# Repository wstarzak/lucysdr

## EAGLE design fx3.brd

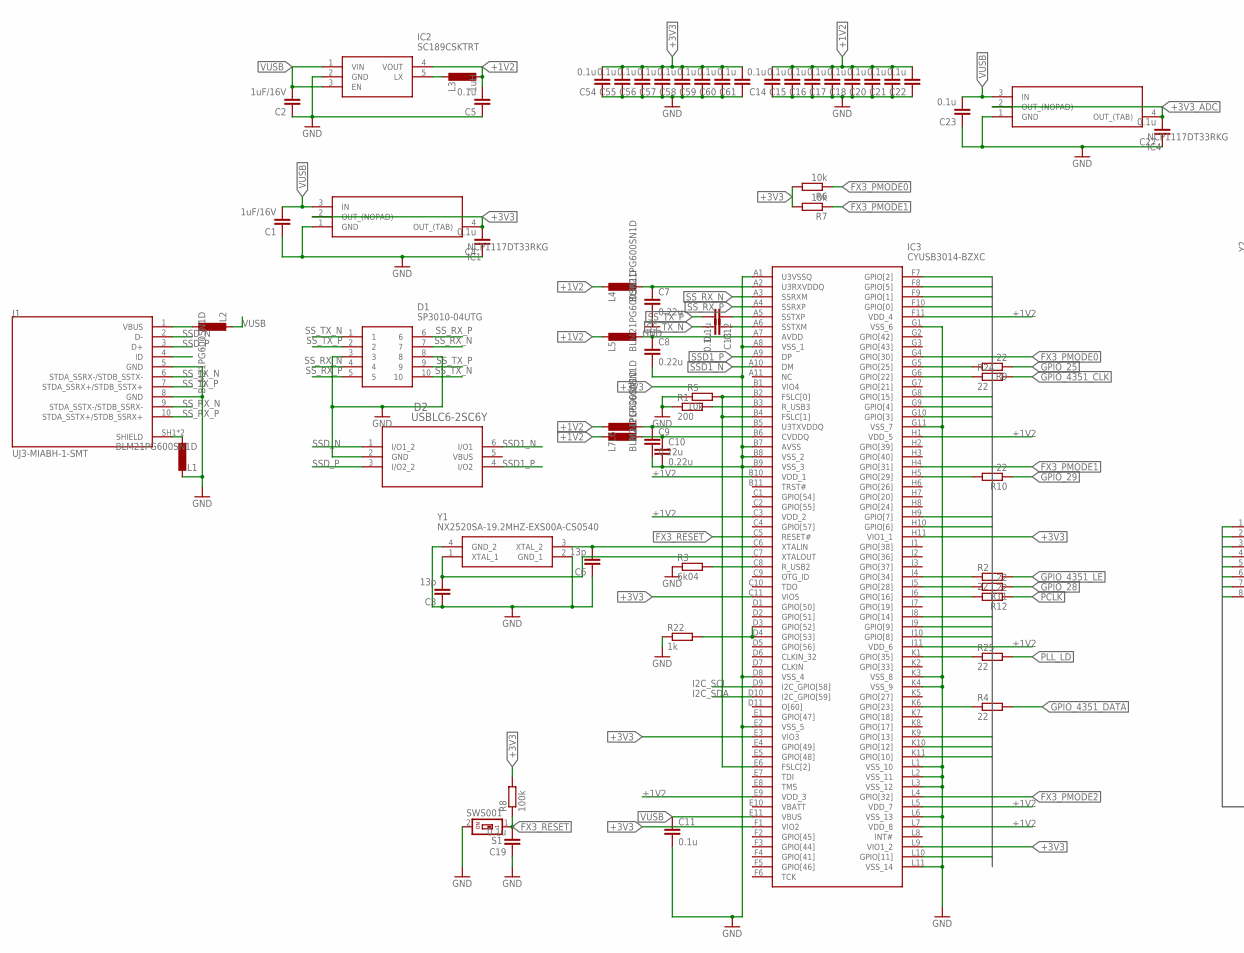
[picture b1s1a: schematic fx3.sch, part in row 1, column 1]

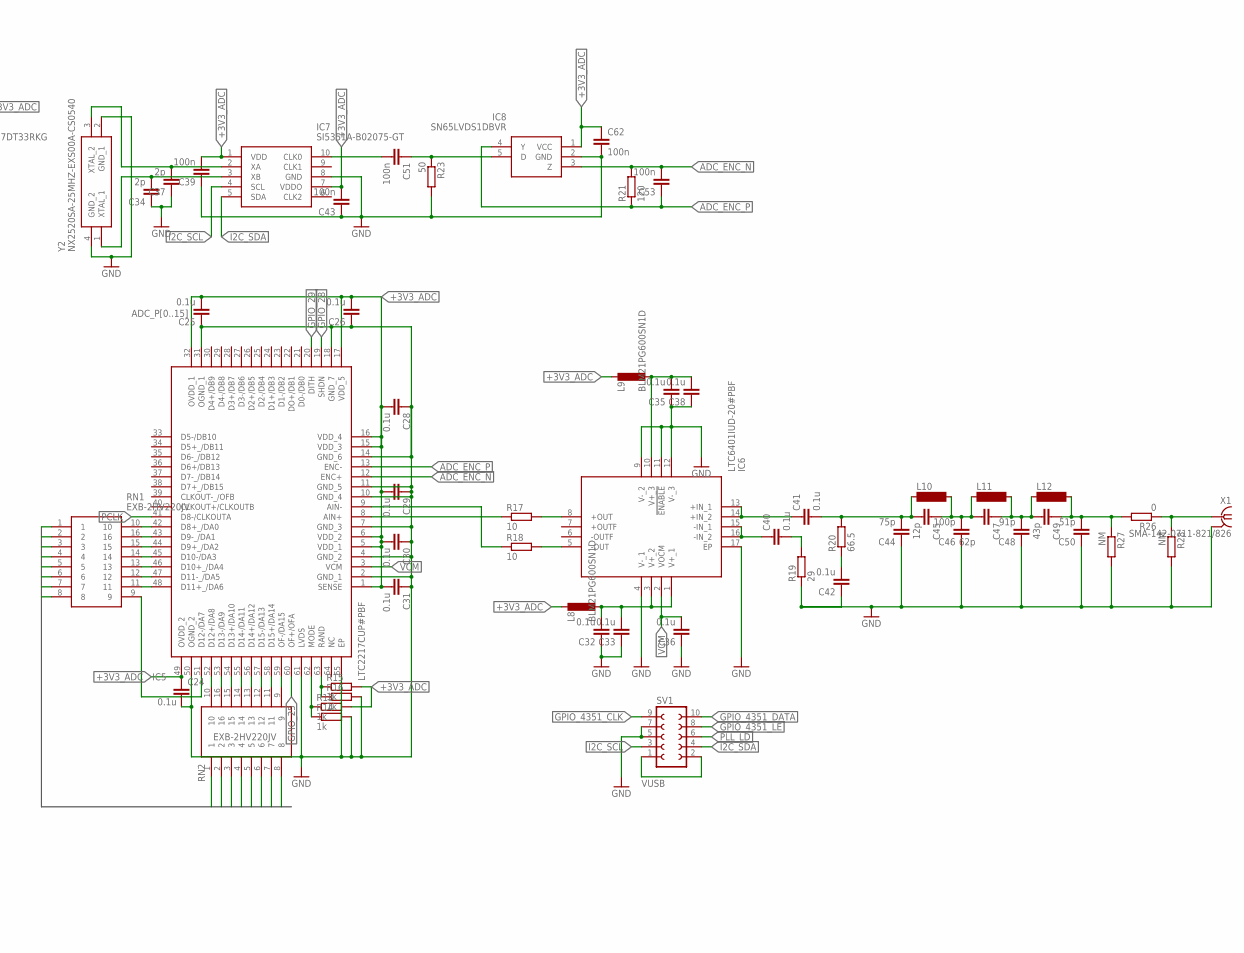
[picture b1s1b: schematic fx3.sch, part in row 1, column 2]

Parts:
C1, C2: 1uF/16V; C0603
C3, C6: 13p; C0603
C4, C5, C11, C12, C13, C14, C15, C16, C17, C18, C19, C20, C21, C22, C23, C24, C25, C26, C27, C28, C29, C30, C31, C32, C33, C35, C36, C38, C40, C41, C42, C54, C55, C56, C57, C58, C59, C60, C61: 0.1u; C0603
C7, C8, C9, C10: 0.22u; C0603
C34, C37: 2p; C0603
C39, C43, C51, C53, C62: 100n; C0603
C44: 75p; C0603
C45: 12p; C0603
C46: 100p; C0603
C47: 62p; C0603
C48: 91p; C0603
C49: 43p; C0603
C50: 51p; C0603
D1: SP3010-04UTG; UDFN-10
D2: USBLC6-2SC6Y; SOT23-6L_STM
IC1, IC4: NCP1117DT33RKG; TO229P990X238-4N
IC2: SC189CSKTRT; SOT95P280X145-5N
IC3: CYUSB3014-BZXC; BGA121C80P11X11_1000X1000X120
IC5: LTC2217CUP#PBF; QFN50P900X900X80-65N
IC6: LTC6401IUD-20#PBF; QFN50P300X300X80-17N
IC7: SI5351A-B02075-GT; SOP50P490X110-10N
IC8: SN65LVDS1DBVR; SOT95P280X145-5N
J1: UJ3-MIABH-1-SMT; CUI_UJ3-MIABH-1-SMT
L1, L2, L4, L5, L6, L7, L8, L9: BLM21PG600SN1D; BLM21AG102BH1J
L3: 1uH; BLM21AG102BH1J
L10, L11, L12: MS85
R1: 200; R0603
R2, R4, R9, R10, R11, R12, R24, R25: 22; R0603
R3: 6k04; R0603
R5, R6, R7: 10k; R0603
R8: 100k; R0603
R13, R14, R15, R16, R22: 1k; R0603
R17, R18: 10; R0603
R19: 29; R0603
R20: 66.5; R0603
R21: 120; R0603
R23: 50; R0603
R26: 0; R0603
R27, R28: NM; R0603
RN1, RN2: EXB-2HV220JV; EXB2HV220JV
S1: SWS001; SMS-001
SV1: FE05-2
X1: SMA-142-0711-821/826; J502-ND-142-0711-821/826
Y1: NX2520SA-19.2MHZ-EXS00A-CS0540; NX2520SA192MHZEXS00ACS05400
Y2: NX2520SA-25MHZ-EXS00A-CS0540; NX2520SA192MHZEXS00ACS05400

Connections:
+1V2: C5.2, C14.2, C15.2, C16.2, C17.2, C18.2, C20.2, C21.2, C22.2, IC2.4 (VOUT), IC3.B10 (VDD_1), IC3.C3 (VDD_2), IC3.E9 (VDD_3), IC3.F11 (VDD_4), IC3.H1 (VDD_5), IC3.J11 (VDD_6), IC3.L5 (VDD_7), IC3.L7 (VDD_8), L3.2, L4.1, L5.1, L6.1, L7.1
+3V3: C4.2, C54.2, C55.2, C56.2, C57.2, C58.2, C59.2, C60.2, C61.2, IC1.2 (OUT_(NOPAD)), IC1.4 (OUT_(TAB)), IC3.B1 (VIO4), IC3.C11 (VIO5), IC3.E3 (VIO3), IC3.F1 (VIO2), IC3.H11 (VIO1_1), IC3.L9 (VIO1_2), R6.2, R7.2, R8.2
+3V3_ADC: C24.1, C25.2, C26.2, C27.2, C28.2, C29.2, C30.2, C31.2, C39.2, C43.2, C62.1, IC4.2 (OUT_(NOPAD)), IC4.4 (OUT_(TAB)), IC5.1 (SENSE), IC5.5 (VDD_1), IC5.6 (VDD_2), IC5.15 (VDD_3), IC5.16 (VDD_4), IC5.17 (VDD_5), IC5.32 (OVDD_1), IC5.49 (OVDD_2), IC7.1 (VDD), IC7.7 (VDDO), IC8.1 (VCC), L8.1, L9.1, R13.2, R15.2
ADC_ENC_N: C53.2, IC5.12 (ENC+), IC8.3 (Z), R21.2
ADC_ENC_P: C53.1, IC5.13 (ENC-), IC8.4 (Y), R21.1
ADC_P0: IC3.F10 (GPIO[0]), RN1.1
ADC_P1: IC3.F9 (GPIO[1]), RN1.2
ADC_P2: IC3.F7 (GPIO[2]), RN1.3
ADC_P3: IC3.G10 (GPIO[3]), RN1.4
ADC_P4: IC3.G9 (GPIO[4]), RN1.5
ADC_P5: IC3.F8 (GPIO[5]), RN1.6
ADC_P6: IC3.H10 (GPIO[6]), RN1.7
ADC_P7: IC3.H9 (GPIO[7]), RN1.8
ADC_P8: IC3.J10 (GPIO[8]), RN2.1
ADC_P9: IC3.J9 (GPIO[9]), RN2.2
ADC_P10: IC3.K11 (GPIO[10]), RN2.3
ADC_P11: IC3.L10 (GPIO[11]), RN2.4
ADC_P12: IC3.K10 (GPIO[12]), RN2.5
ADC_P13: IC3.K9 (GPIO[13]), RN2.6
ADC_P14: IC3.J8 (GPIO[14]), RN2.7
ADC_P15: IC3.G8 (GPIO[15]), RN2.8
AVDD_A7: C8.1, IC3.A7 (AVDD), L5.2
CVDDQ_B6: C10.1, IC3.B6 (CVDDQ), L7.2
FX3_PMODE0: IC3.G4 (GPIO[30]), R6.1
FX3_PMODE1: IC3.H4 (GPIO[31]), R7.1
FX3_PMODE2: IC3.L4 (GPIO[32])
FX3_RESET: C19.2, IC3.C5 (RESET#), R8.1, S1.1
GND: C1.1, C2.1, C3.1, C4.1, C5.1, C6.1, C7.2, C8.2, C9.2, C10.2, C11.2, C14.1, C15.1, C16.1, C17.1, C18.1, C19.1, C20.1, C21.1, C22.1, C23.1, C24.2, C25.1, C26.1, C27.1, C28.1, C29.1, C30.1, C31.1, C32.1, C33.1, C34.1, C35.1, C36.1, C37.1, C38.1, C39.1, C42.1, C43.1, C44.1, C46.1, C48.1, C50.1, C54.1, C55.1, C56.1, C57.1, C58.1, C59.1, C60.1, C61.1, C62.2, D1.3, D1.8, D2.2 (GND), IC1.1 (GND), IC2.2 (GND), IC3.A1 (U3VSSQ), IC3.A8 (VSS_1), IC3.B7 (AVSS), IC3.B8 (VSS_2), IC3.B9 (VSS_3), IC3.D8 (VSS_4), IC3.E2 (VSS_5), IC3.G1 (VSS_6), IC3.G11 (VSS_7), IC3.K3 (VSS_8), IC3.K4 (VSS_9), IC3.L1 (VSS_10), IC3.L2 (VSS_11), IC3.L3 (VSS_12), IC3.L6 (VSS_13), IC3.L11 (VSS_14), IC4.1 (GND), IC5.2 (GND_1), IC5.4 (GND_2), IC5.7 (GND_3), IC5.10 (GND_4), IC5.11 (GND_5), IC5.14 (GND_6), IC5.18 (GND_7), IC5.31 (OGND_1), IC5.50 (OGND_2), IC5.61 (LVDS), IC5.65 (EP), IC6.4 (V-_1), IC6.9 (V-_2), IC6.11 (!ENABLE), IC6.12 (V-_3), IC6.17 (EP), IC7.8 (GND), IC8.2 (GND), J1.5 (GND), J1.8 (GND), L1.1, R1.1, R3.1, R5.1, R14.2, R16.2, R19.1, R22.1, R23.2, R27.2, R28.2, S1.2, SV1.5, SV1.7, X1.G@1 (2), X1.G@2 (2), X1.G@3 (2), X1.G@4 (2), Y1.2 (GND_1), Y1.4 (GND_2), Y2.2 (GND_1), Y2.4 (GND_2)
GPIO_25: IC5.60 (OF+/OFA), R9.1
GPIO_28: IC5.19 (SHDN), R11.1
GPIO_29: IC5.20 (DITH), R10.1
GPIO_4351_CLK: R24.2, SV1.9
GPIO_4351_DATA: R4.2, SV1.10
GPIO_4351_LE: R2.2, SV1.8
I2C_SCL: IC3.D9 (I2C_GPIO[58]), IC7.4 (SCL), SV1.3
I2C_SDA: IC3.D10 (I2C_GPIO[59]), IC7.5 (SDA), SV1.4
unnamed: C40.1, IC6.15 (-IN_1), IC6.16 (-IN_2)
unnamed: C47.1, C48.2, C49.2, L11.2, L12.1
unnamed: C41.1, IC6.13 (+IN_1), IC6.14 (+IN_2)
unnamed: C40.2, R19.2
unnamed: C41.2, C44.2, C45.2, L10.1, R20.2
unnamed: C42.2, R20.1
unnamed: IC6.5 (-OUT), R18.2
unnamed: IC6.8 (+OUT), R17.2
unnamed: IC5.8 (AIN+), R17.1
unnamed: IC5.9 (AIN-), R18.1
unnamed: IC3.K6 (GPIO[23]), R4.1
unnamed: C49.1, C50.2, L12.2, R26.2, R27.1
unnamed: C45.1, C46.2, C47.2, L10.2, L11.1
unnamed: C37.2, IC7.2 (XA), Y2.3 (XTAL_2)
unnamed: C6.2, IC3.C6 (XTALIN), Y1.3 (XTAL_2)
unnamed: C3.2, IC3.C7 (XTALOUT), Y1.1 (XTAL_1)
unnamed: IC3.J4 (GPIO[34]), R2.1
unnamed: IC5.59 (OF-/DA15), RN2.9
unnamed: IC5.51 (D12-/DA7), RN1.9
unnamed: IC5.52 (D12+/DA8), RN2.10
unnamed: IC5.53 (D13-/DA9), RN2.16
unnamed: IC5.54 (D13+/DA10), RN2.15
unnamed: IC5.55 (D14-/DA11), RN2.14
unnamed: IC5.56 (D14+/DA12), RN2.13
unnamed: IC5.57 (D15-/DA13), RN2.12
unnamed: IC5.58 (D15+/DA14), RN2.11
unnamed: IC5.48 (D11+_/DA6), RN1.11
unnamed: IC5.47 (D11-_/DA5), RN1.12
unnamed: IC5.46 (D10+_/DA4), RN1.13
unnamed: IC5.45 (D10-/DA3), RN1.14
unnamed: IC5.44 (D9+_/DA2), RN1.15
unnamed: IC5.43 (D9-_/DA1), RN1.16
unnamed: IC5.42 (D8+_/DA0), RN1.10
unnamed: IC5.62 (MODE), R13.1, R14.1
unnamed: IC3.H5 (GPIO[29]), R10.2
unnamed: IC5.63 (RAND), R15.1, R16.1
unnamed: IC3.J6 (GPIO[16]), R12.2
unnamed: IC3.J5 (GPIO[28]), R11.2
unnamed: IC3.G5 (GPIO[25]), R9.2
unnamed: J1.SH1 (SHIELD), J1.SH2 (SHIELD), L1.2
unnamed: J1.1 (VBUS), L2.2
unnamed: C51.2, IC7.10 (CLK0)
unnamed: C51.1, IC8.5 (D), R23.1
unnamed: IC3.D3 (GPIO[52]), IC3.D4 (GPIO[53]), R22.2
unnamed: IC3.G6 (GPIO[22]), R24.1
unnamed: C13.1, IC3.A6 (SSTXM)
unnamed: C12.1, IC3.A5 (SSTXP)
unnamed: IC3.B2 (FSLC[0]), IC3.B4 (FSLC[1]), IC3.E6 (FSLC[2]), R5.2
unnamed: IC3.C8 (R_USB2), R3.2
unnamed: IC3.B3 (R_USB3), R1.2
unnamed: C34.2, IC7.3 (XB), Y2.1 (XTAL_1)
unnamed: IC3.K1 (GPIO[35]), R25.1
unnamed: IC2.5 (LX), L3.1
unnamed: R26.1, R28.1, X1.1
PCLK: IC5.41 (D8-/CLKOUTA), R12.1
PLL_LD: R25.2, SV1.6
SSD1_N: D2.6 (I/O1), IC3.A10 (DM)
SSD1_P: D2.4 (I/O2), IC3.A9 (DP)
SSD_N: D2.1 (I/O1_2), J1.2 (D-)
SSD_P: D2.3 (I/O2_2), J1.3 (D+)
SS_RX_N: D1.4, D1.7, IC3.A3 (SSRXM), J1.9 (STDA_SSTX-/STDB_SSRX-)
SS_RX_P: D1.5, D1.6, IC3.A4 (SSRXP), J1.10 (STDA_SSTX+/STDB_SSRX+)
SS_TX_N: C13.2, D1.1, D1.10, J1.6 (STDA_SSRX-/STDB_SSTX-)
SS_TX_P: C12.2, D1.2, D1.9, J1.7 (STDA_SSRX+/STDB_SSTX+)
U3RXV_A2: C7.1, IC3.A2 (U3RXVDDQ), L4.2
U3TXVDDQ_B5: C9.1, IC3.B5 (U3TXVDDQ), L6.2
VBUS: D2.5 (VBUS)
VCM: C36.2, IC5.3 (VCM), IC6.2 (VOCM)
VPROR: C32.2, C33.2, C35.2, C38.2, IC6.1 (V+_1), IC6.3 (V+_2), IC6.10 (V+_3), L8.2, L9.2
VUSB: C1.2, C2.2, C11.1, C23.2, IC1.3 (IN), IC2.1 (VIN), IC2.3 (EN), IC3.E11 (VBUS), IC4.3 (IN), L2.1, SV1.1, SV1.2

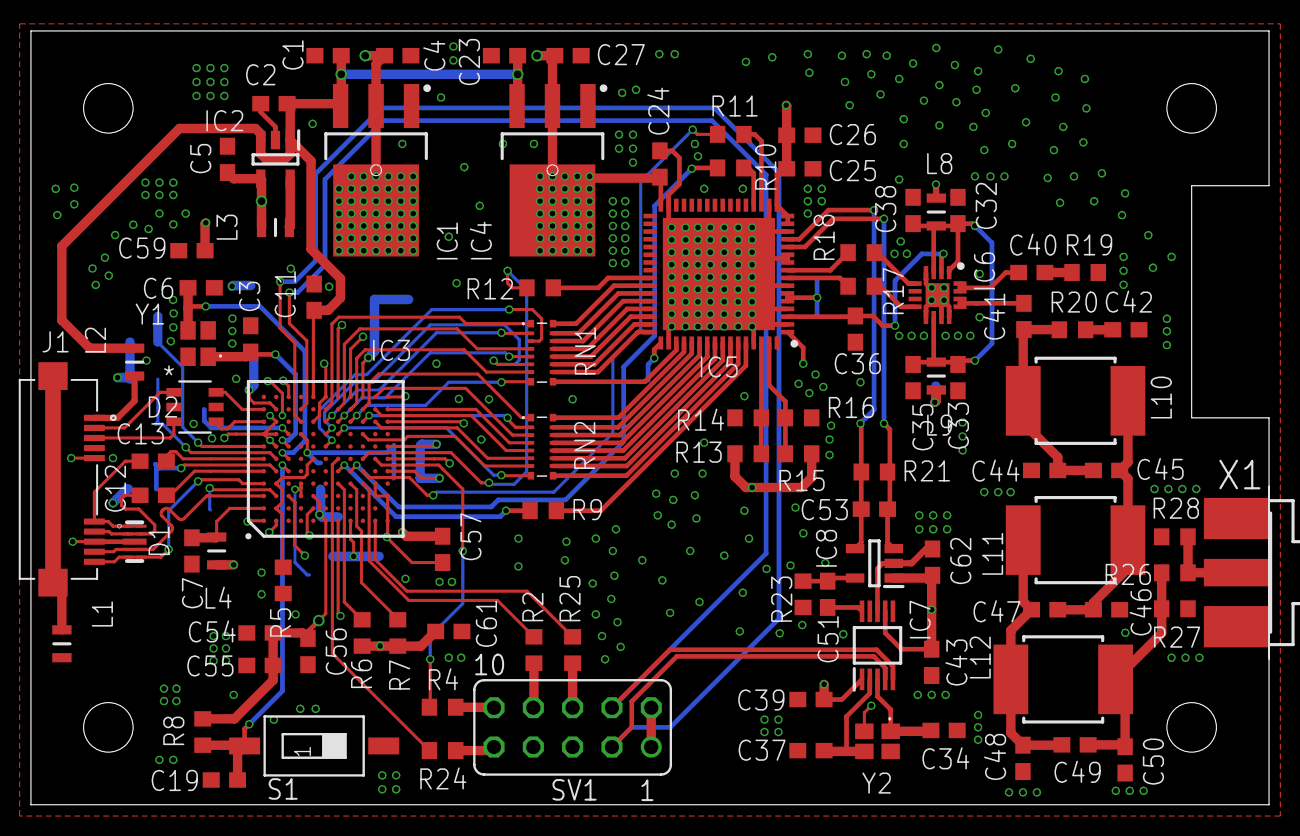
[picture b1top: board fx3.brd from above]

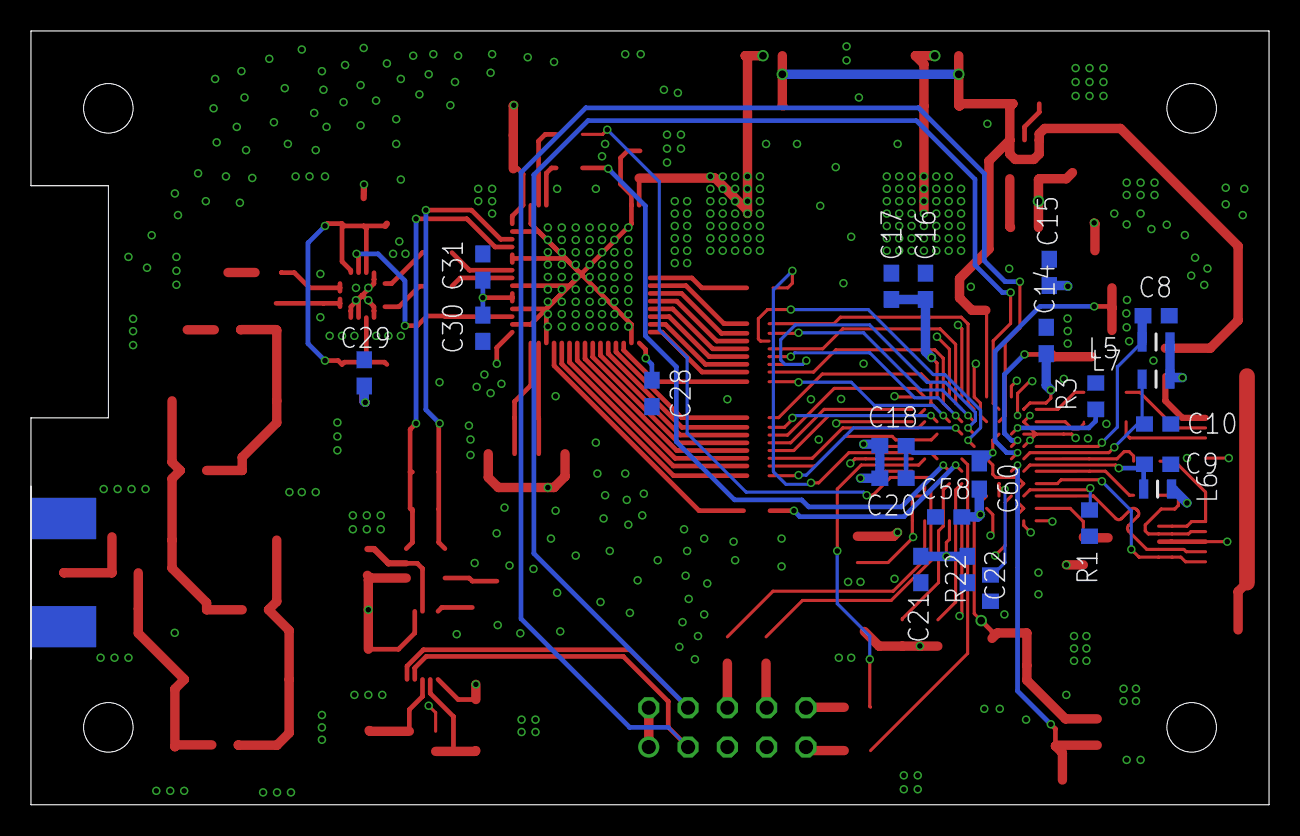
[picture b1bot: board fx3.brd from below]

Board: 4 copper layers, 80.0 x 50.0 mm, 119 parts (23 on the bottom side), 104 nets.
